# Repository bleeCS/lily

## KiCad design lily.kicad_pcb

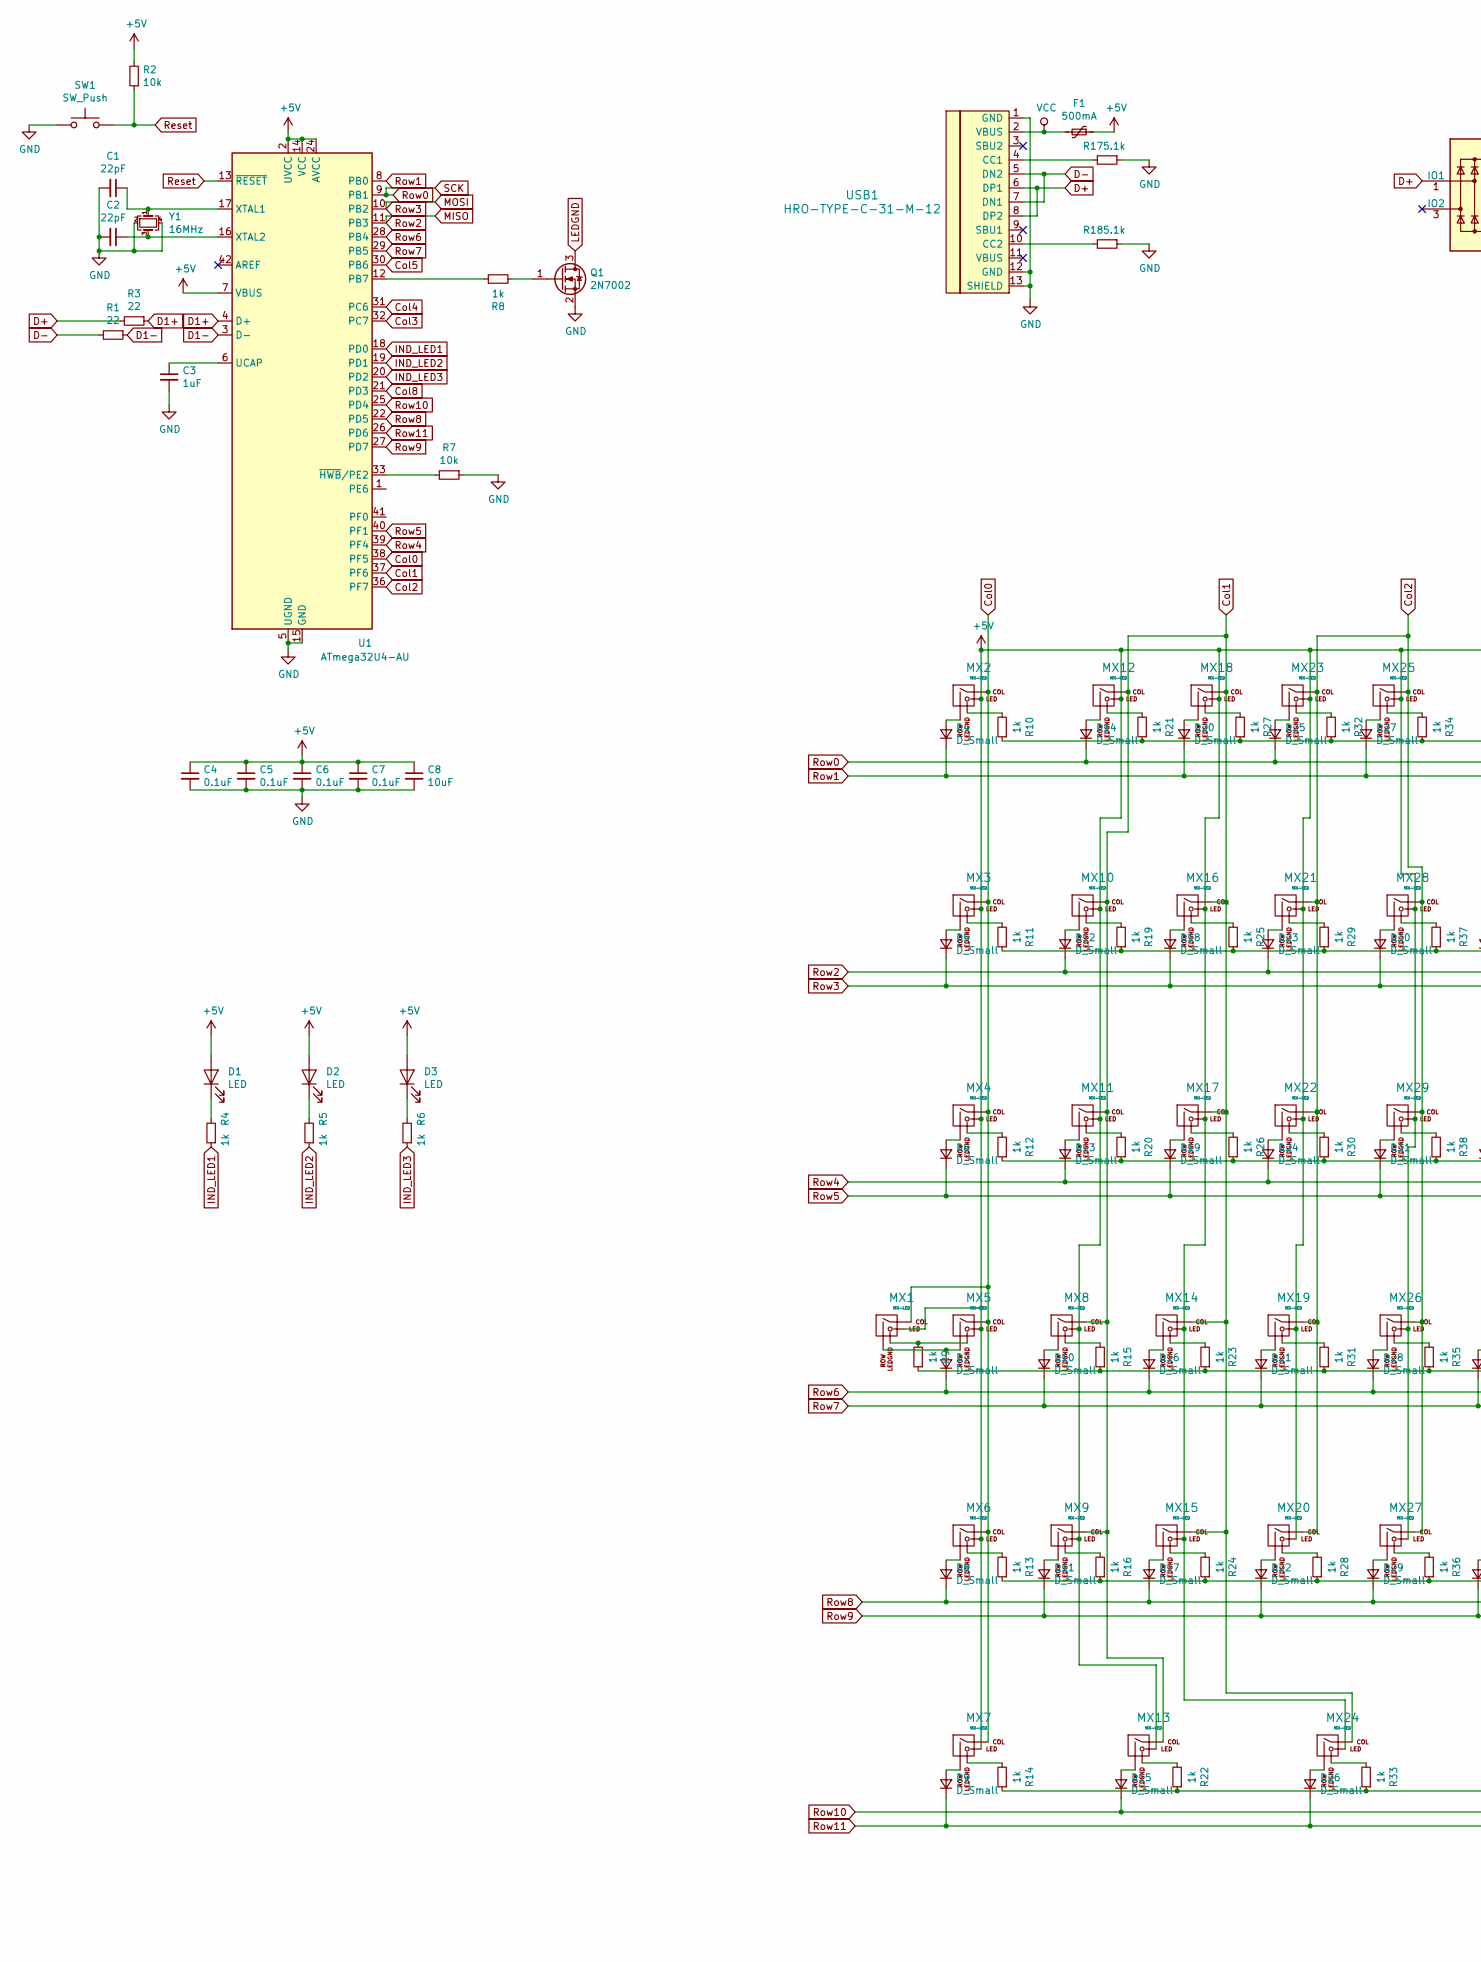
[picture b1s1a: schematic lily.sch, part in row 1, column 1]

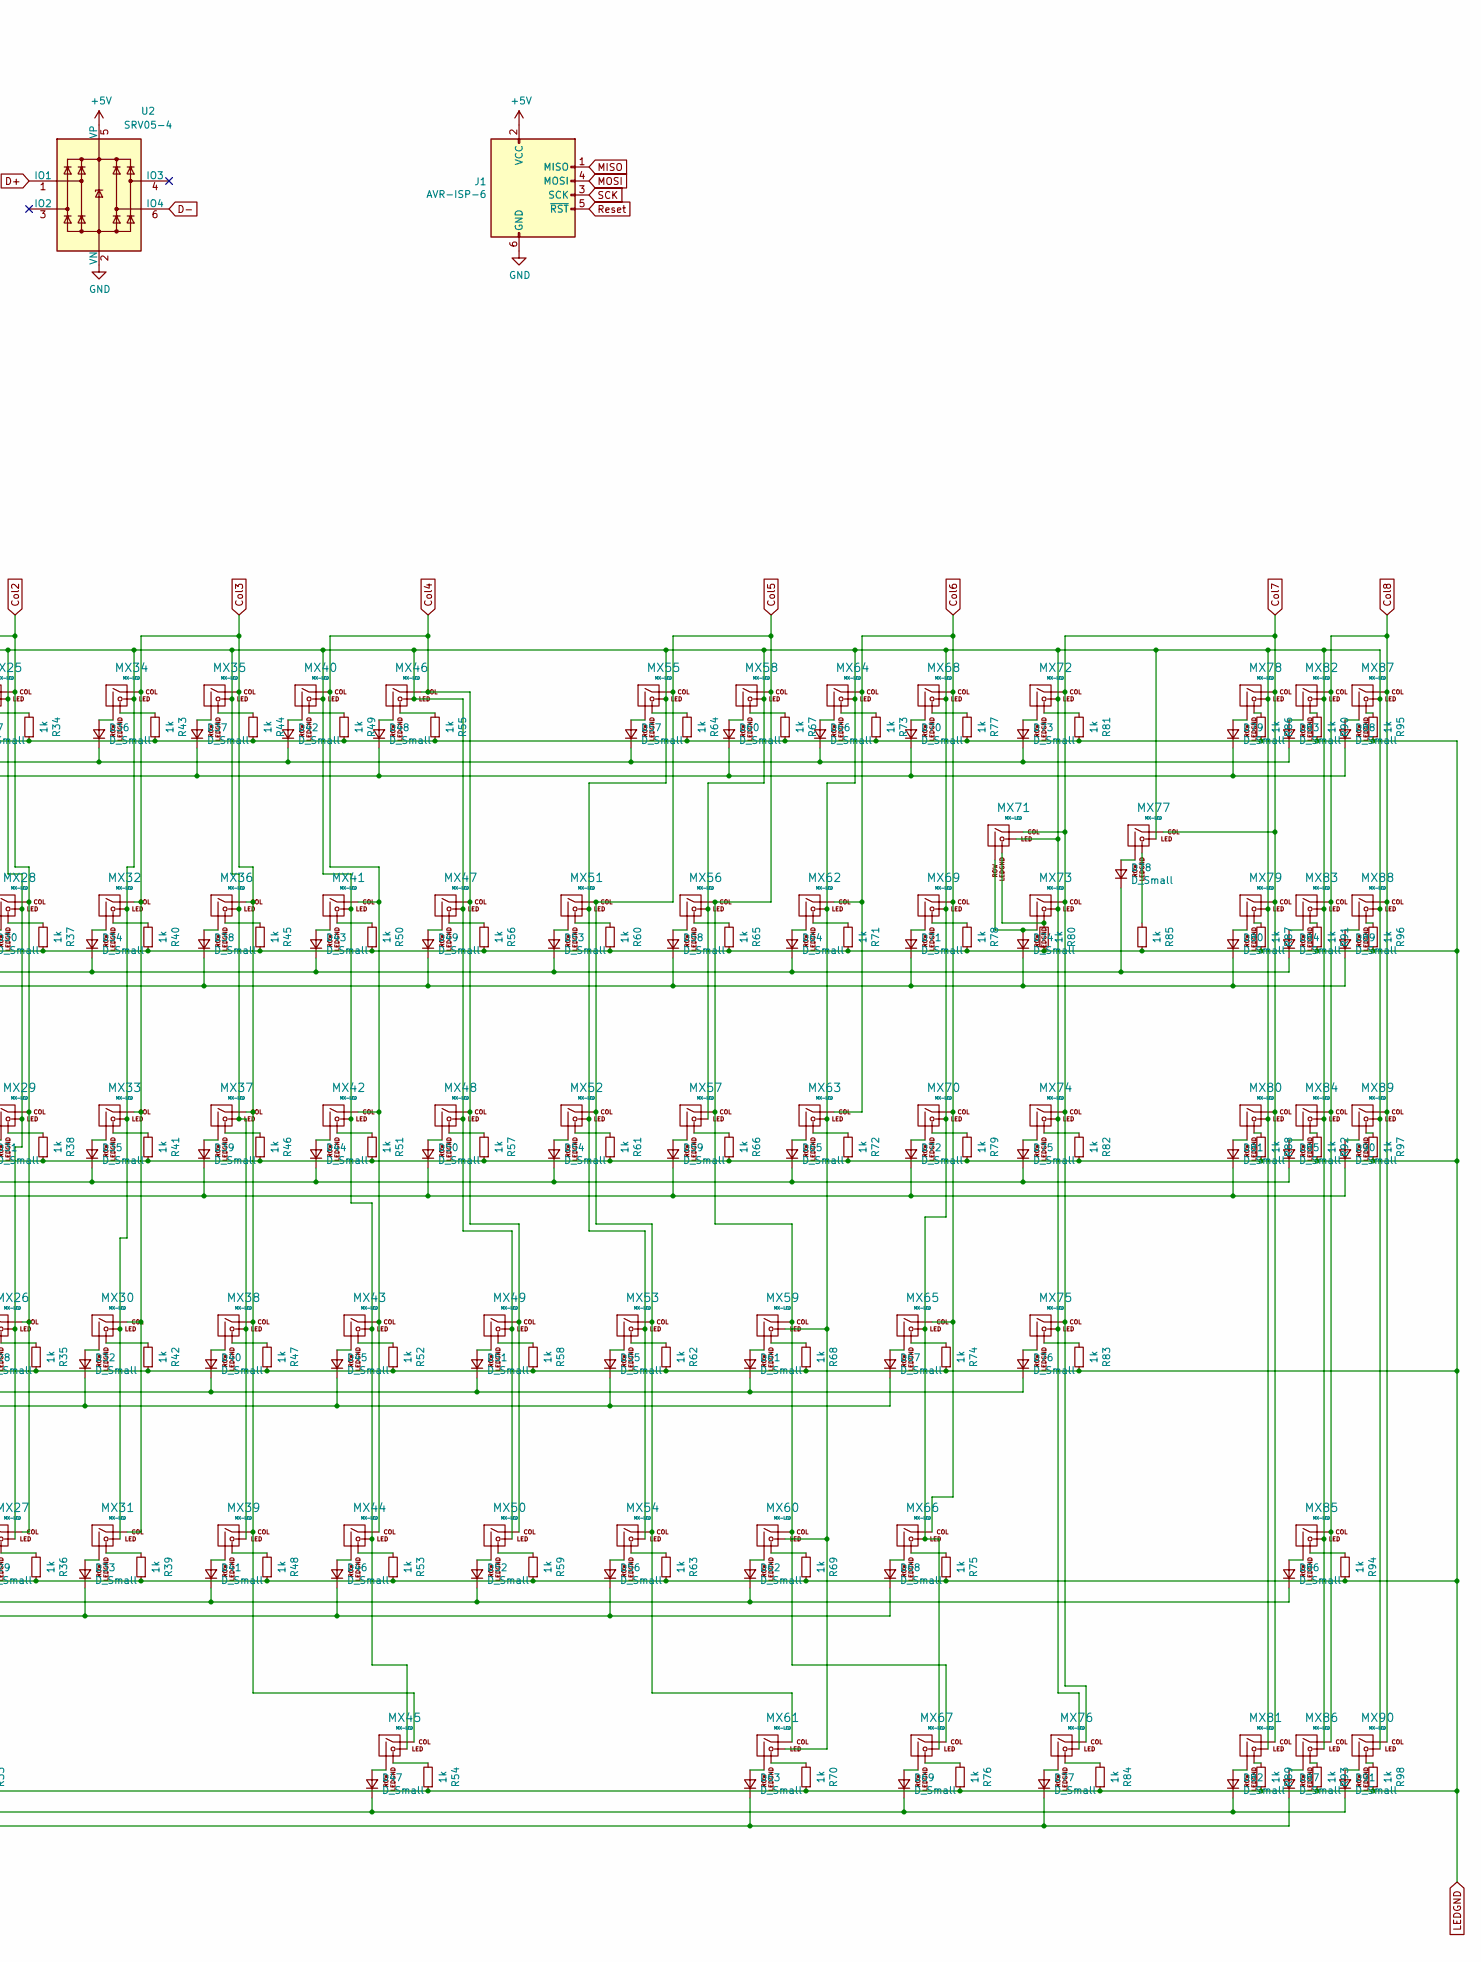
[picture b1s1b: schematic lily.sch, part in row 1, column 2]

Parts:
C1, C2: 22pF; C_0805_2012Metric
C3: 1uF; C_0805_2012Metric
C4, C5, C6, C7: 0.1uF; C_0805_2012Metric
C8: 10uF; C_0805_2012Metric
D1, D2, D3: LED; LED_D1.8mm_W3.3mm_H2.4mm
D4, D5, D6, D7, D8, D9, D10, D11, D12, D13, D14, D15, D16, D17, D18, D19, D20, D21, D22, D23, D24, D25, D26, D27, D28, D29, D30, D31, D32, D33, D34, D35, D36, D37, D38, D39, D40, D41, D42, D43, D44, D45, D46, D47, D48, D49, D50, D51, D52, D53, D54, D55, D56, D57, D58, D59, D60, D61, D62, D63, D64, D65, D66, D67, D68, D69, D70, D71, D72, D73, D74, D75, D76, D77, D78, D79, D80, D81, D82, D83, D84, D85, D86, D87, D88, D89, D90, D91: D_Small; D_SOD-123
F1: 500mA; Fuse_1206_3216Metric
J1: AVR-ISP-6; PinHeader_2x03_P1.00mm_Vertical
MX1: MX-LED; MXOnly-1.25U
MX2, MX3, MX8, MX9, MX10, MX11, MX12, MX13, MX14, MX15, MX16, MX17, MX18, MX19, MX20, MX21, MX22, MX23, MX25, MX26, MX27, MX28, MX29, MX30, MX31, MX32, MX33, MX34, MX35, MX36, MX37, MX38, MX39, MX40, MX41, MX42, MX43, MX44, MX46, MX47, MX48, MX49, MX50, MX51, MX52, MX53, MX54, MX55, MX56, MX57, MX58, MX59, MX60, MX62, MX63, MX64, MX65, MX67, MX68, MX69, MX70, MX71, MX72, MX77, MX78, MX79, MX80, MX81, MX82, MX83, MX84, MX85, MX86, MX87, MX88, MX89, MX90: MX-LED; MXOnly-1U
MX4, MX7, MX24, MX61, MX74, MX76: MX-LED; MXOnly-1.5U
MX5: MX-LED; MXOnly-1.75U
MX6: MX-LED; MXOnly-2.25U
MX45: MX-LED; MXOnly-7U-ReversedStabilizers
MX66: MX-LED; MXOnly-2.75U
MX73: MX-LED; MXOnly-2U
MX75: MX-LED; MXOnly-2.25U-ReversedStabilizers
Q1: 2N7002; SOT-23
R1, R3: 22; R_0805_2012Metric
R2, R7: 10k; R_0805_2012Metric
R4, R5, R6, R8, R9, R10, R11, R12, R13, R14, R15, R16, R19, R20, R21, R22, R23, R24, R25, R26, R27, R28, R29, R30, R31, R32, R33, R34, R35, R36, R37, R38, R39, R40, R41, R42, R43, R44, R45, R46, R47, R48, R49, R50, R51, R52, R53, R54, R55, R56, R57, R58, R59, R60, R61, R62, R63, R64, R65, R66, R67, R68, R69, R70, R71, R72, R73, R74, R75, R76, R77, R78, R79, R80, R81, R82, R83, R84, R85, R86, R87, R88, R89, R90, R91, R92, R93, R94, R95, R96, R97, R98: 1k; R_0805_2012Metric
R17, R18: 5.1k; R_0805_2012Metric
SW1: SW_Push; SKQG-1155865
U1: ATmega32U4-AU; TQFP-44_10x10mm_P0.8mm
U2: SRV05-4; SOT-23-6
USB1: HRO-TYPE-C-31-M-12
Y1: 16MHz; Crystal_SMD_3225-4Pin_3.2x2.5mm

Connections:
+5V: C4.1, C5.1, C6.1, C7.1, C8.1, D1.2 (A), D2.2 (A), D3.2 (A), F1.1, J1.2 (VCC), MX1.3 (LED), MX2.3 (LED), MX3.3 (LED), MX4.3 (LED), MX5.3 (LED), MX6.3 (LED), MX7.3 (LED), MX8.3 (LED), MX9.3 (LED), MX10.3 (LED), MX11.3 (LED), MX12.3 (LED), MX13.3 (LED), MX14.3 (LED), MX15.3 (LED), MX16.3 (LED), MX17.3 (LED), MX18.3 (LED), MX19.3 (LED), MX20.3 (LED), MX21.3 (LED), MX22.3 (LED), MX23.3 (LED), MX24.3 (LED), MX25.3 (LED), MX26.3 (LED), MX27.3 (LED), MX28.3 (LED), MX29.3 (LED), MX30.3 (LED), MX31.3 (LED), MX32.3 (LED), MX33.3 (LED), MX34.3 (LED), MX35.3 (LED), MX36.3 (LED), MX37.3 (LED), MX38.3 (LED), MX39.3 (LED), MX40.3 (LED), MX41.3 (LED), MX42.3 (LED), MX43.3 (LED), MX44.3 (LED), MX45.3 (LED), MX46.3 (LED), MX47.3 (LED), MX48.3 (LED), MX49.3 (LED), MX50.3 (LED), MX51.3 (LED), MX52.3 (LED), MX53.3 (LED), MX54.3 (LED), MX55.3 (LED), MX56.3 (LED), MX57.3 (LED), MX58.3 (LED), MX59.3 (LED), MX60.3 (LED), MX61.3 (LED), MX62.3 (LED), MX63.3 (LED), MX64.3 (LED), MX65.3 (LED), MX66.3 (LED), MX67.3 (LED), MX68.3 (LED), MX69.3 (LED), MX70.3 (LED), MX71.3 (LED), MX72.3 (LED), MX73.3 (LED), MX74.3 (LED), MX75.3 (LED), MX76.3 (LED), MX77.3 (LED), MX78.3 (LED), MX79.3 (LED), MX80.3 (LED), MX81.3 (LED), MX82.3 (LED), MX83.3 (LED), MX84.3 (LED), MX85.3 (LED), MX86.3 (LED), MX87.3 (LED), MX88.3 (LED), MX89.3 (LED), MX90.3 (LED), R2.2, U1.2 (UVCC), U1.7 (VBUS), U1.14 (VCC), U1.24 (AVCC), U1.34 (VCC), U1.44 (AVCC), U2.5 (VP)
Col0: MX1.1 (COL), MX2.1 (COL), MX3.1 (COL), MX4.1 (COL), MX5.1 (COL), MX6.1 (COL), MX7.1 (COL), U1.38 (PF5)
Col1: MX8.1 (COL), MX9.1 (COL), MX10.1 (COL), MX11.1 (COL), MX12.1 (COL), MX13.1 (COL), MX14.1 (COL), MX15.1 (COL), MX16.1 (COL), MX17.1 (COL), MX18.1 (COL), MX24.1 (COL), U1.37 (PF6)
Col2: MX19.1 (COL), MX20.1 (COL), MX21.1 (COL), MX22.1 (COL), MX23.1 (COL), MX25.1 (COL), MX26.1 (COL), MX27.1 (COL), MX28.1 (COL), MX29.1 (COL), U1.36 (PF7)
Col3: MX30.1 (COL), MX31.1 (COL), MX32.1 (COL), MX33.1 (COL), MX34.1 (COL), MX35.1 (COL), MX36.1 (COL), MX37.1 (COL), MX38.1 (COL), MX39.1 (COL), MX45.1 (COL), U1.32 (PC7)
Col4: MX40.1 (COL), MX41.1 (COL), MX42.1 (COL), MX43.1 (COL), MX44.1 (COL), MX46.1 (COL), MX47.1 (COL), MX48.1 (COL), MX49.1 (COL), MX50.1 (COL), U1.31 (PC6)
Col5: MX51.1 (COL), MX52.1 (COL), MX53.1 (COL), MX54.1 (COL), MX55.1 (COL), MX56.1 (COL), MX57.1 (COL), MX58.1 (COL), MX59.1 (COL), MX60.1 (COL), MX61.1 (COL), MX67.1 (COL), U1.30 (PB6)
Col6: MX62.1 (COL), MX63.1 (COL), MX64.1 (COL), MX65.1 (COL), MX66.1 (COL), MX68.1 (COL), MX69.1 (COL), MX70.1 (COL)
Col7: MX71.1 (COL), MX72.1 (COL), MX73.1 (COL), MX74.1 (COL), MX75.1 (COL), MX76.1 (COL), MX77.1 (COL), MX78.1 (COL), MX79.1 (COL), MX80.1 (COL), MX81.1 (COL)
Col8: MX82.1 (COL), MX83.1 (COL), MX84.1 (COL), MX85.1 (COL), MX86.1 (COL), MX87.1 (COL), MX88.1 (COL), MX89.1 (COL), MX90.1 (COL), U1.21 (PD3)
D1+: R3.1, U1.4 (D+)
D1-: R1.1, U1.3 (D-)
D+: R3.2, U2.1 (IO1), USB1.6 (DP1), USB1.8 (DP2)
D-: R1.2, U2.6 (IO4), USB1.5 (DN2), USB1.7 (DN1)
GND: C1.2, C2.2, C3.2, C4.2, C5.2, C6.2, C7.2, C8.2, J1.6 (GND), Q1.2 (S), R7.1, R17.1, R18.1, SW1.1, U1.5 (UGND), U1.15 (GND), U1.23 (GND), U1.35 (GND), U1.43 (GND), U2.2 (VN), USB1.1 (GND), USB1.12 (GND), USB1.13 (SHIELD), Y1.2, Y1.4
IND_LED1: R4.1, U1.18 (PD0)
IND_LED2: R5.1, U1.19 (PD1)
IND_LED3: R6.1, U1.20 (PD2)
LEDGND: Q1.3 (D), R9.1, R10.1, R11.1, R12.1, R13.1, R14.1, R15.1, R16.1, R19.1, R20.1, R21.1, R22.1, R23.1, R24.1, R25.1, R26.1, R27.1, R28.1, R29.1, R30.1, R31.1, R32.1, R33.1, R34.1, R35.1, R36.1, R37.1, R38.1, R39.1, R40.1, R41.1, R42.1, R43.1, R44.1, R45.1, R46.1, R47.1, R48.1, R49.1, R50.1, R51.1, R52.1, R53.1, R54.1, R55.1, R56.1, R57.1, R58.1, R59.1, R60.1, R61.1, R62.1, R63.1, R64.1, R65.1, R66.1, R67.1, R68.1, R69.1, R70.1, R71.1, R72.1, R73.1, R74.1, R75.1, R76.1, R77.1, R78.1, R79.1, R80.1, R81.1, R82.1, R83.1, R84.1, R85.1, R86.1, R87.1, R88.1, R89.1, R90.1, R91.1, R92.1, R93.1, R94.1, R95.1, R96.1, R97.1, R98.1
MISO: D12.1 (K), D23.1 (K), D34.1 (K), D43.1 (K), D53.1 (K), D64.1 (K), D78.1 (K), D84.1 (K), J1.1 (MISO), U1.11 (PB3)
MOSI: D5.1 (K), D18.1 (K), D30.1 (K), D38.1 (K), D49.1 (K), D58.1 (K), D71.1 (K), D74.1 (K), D80.1 (K), D89.1 (K), J1.4 (MOSI), U1.10 (PB2)
unnamed: C1.1, U1.17 (XTAL1), Y1.1
unnamed: C2.1, U1.16 (XTAL2), Y1.3
unnamed: C3.1, U1.6 (UCAP)
unnamed: D1.1 (K), R4.2
unnamed: D2.1 (K), R5.2
unnamed: D3.1 (K), R6.2
unnamed: D4.2 (A), MX2.2 (ROW)
unnamed: D5.2 (A), MX3.2 (ROW)
unnamed: D6.2 (A), MX4.2 (ROW)
unnamed: D7.2 (A), MX1.2 (ROW), MX5.2 (ROW)
unnamed: D8.2 (A), MX6.2 (ROW)
unnamed: D9.2 (A), MX7.2 (ROW)
unnamed: D10.2 (A), MX8.2 (ROW)
unnamed: D11.2 (A), MX9.2 (ROW)
unnamed: D12.2 (A), MX10.2 (ROW)
unnamed: D13.2 (A), MX11.2 (ROW)
unnamed: D14.2 (A), MX12.2 (ROW)
unnamed: D15.2 (A), MX13.2 (ROW)
unnamed: D16.2 (A), MX14.2 (ROW)
unnamed: D17.2 (A), MX15.2 (ROW)
unnamed: D18.2 (A), MX16.2 (ROW)
unnamed: D19.2 (A), MX17.2 (ROW)
unnamed: D20.2 (A), MX18.2 (ROW)
unnamed: D21.2 (A), MX19.2 (ROW)
unnamed: D22.2 (A), MX20.2 (ROW)
unnamed: D23.2 (A), MX21.2 (ROW)
unnamed: D24.2 (A), MX22.2 (ROW)
unnamed: D25.2 (A), MX23.2 (ROW)
unnamed: D26.2 (A), MX24.2 (ROW)
unnamed: D27.2 (A), MX25.2 (ROW)
unnamed: D28.2 (A), MX26.2 (ROW)
unnamed: D29.2 (A), MX27.2 (ROW)
unnamed: D30.2 (A), MX28.2 (ROW)
unnamed: D31.2 (A), MX29.2 (ROW)
unnamed: D32.2 (A), MX30.2 (ROW)
unnamed: D33.2 (A), MX31.2 (ROW)
unnamed: D34.2 (A), MX32.2 (ROW)
unnamed: D35.2 (A), MX33.2 (ROW)
unnamed: D36.2 (A), MX34.2 (ROW)
unnamed: D37.2 (A), MX35.2 (ROW)
unnamed: D38.2 (A), MX36.2 (ROW)
unnamed: D39.2 (A), MX37.2 (ROW)
unnamed: D40.2 (A), MX38.2 (ROW)
unnamed: D41.2 (A), MX39.2 (ROW)
unnamed: D42.2 (A), MX40.2 (ROW)
unnamed: D43.2 (A), MX41.2 (ROW)
unnamed: D44.2 (A), MX42.2 (ROW)
unnamed: D45.2 (A), MX43.2 (ROW)
unnamed: D46.2 (A), MX44.2 (ROW)
unnamed: D47.2 (A), MX45.2 (ROW)
unnamed: D48.2 (A), MX46.2 (ROW)
unnamed: D49.2 (A), MX47.2 (ROW)
unnamed: D50.2 (A), MX48.2 (ROW)
unnamed: D51.2 (A), MX49.2 (ROW)
unnamed: D52.2 (A), MX50.2 (ROW)
unnamed: D53.2 (A), MX51.2 (ROW)
unnamed: D54.2 (A), MX52.2 (ROW)
unnamed: D55.2 (A), MX53.2 (ROW)
unnamed: D56.2 (A), MX54.2 (ROW)
unnamed: D57.2 (A), MX55.2 (ROW)
unnamed: D58.2 (A), MX56.2 (ROW)
unnamed: D59.2 (A), MX57.2 (ROW)
unnamed: D60.2 (A), MX58.2 (ROW)
unnamed: D61.2 (A), MX59.2 (ROW)
unnamed: D62.2 (A), MX60.2 (ROW)
unnamed: D63.2 (A), MX61.2 (ROW)
unnamed: D64.2 (A), MX62.2 (ROW)
unnamed: D65.2 (A), MX63.2 (ROW)
unnamed: D66.2 (A), MX64.2 (ROW)
unnamed: D67.2 (A), MX65.2 (ROW)
unnamed: D68.2 (A), MX66.2 (ROW)
unnamed: D69.2 (A), MX67.2 (ROW)
unnamed: D70.2 (A), MX68.2 (ROW)
unnamed: D71.2 (A), MX69.2 (ROW)
unnamed: D72.2 (A), MX70.2 (ROW)
unnamed: D73.2 (A), MX72.2 (ROW)
unnamed: D74.2 (A), MX71.2 (ROW), MX73.2 (ROW)
unnamed: D75.2 (A), MX74.2 (ROW)
unnamed: D76.2 (A), MX75.2 (ROW)
unnamed: D77.2 (A), MX76.2 (ROW)
unnamed: D78.2 (A), MX77.2 (ROW)
unnamed: D79.2 (A), MX78.2 (ROW)
unnamed: D80.2 (A), MX79.2 (ROW)
unnamed: D81.2 (A), MX80.2 (ROW)
unnamed: D82.2 (A), MX81.2 (ROW)
unnamed: D83.2 (A), MX82.2 (ROW)
unnamed: D84.2 (A), MX83.2 (ROW)
unnamed: D85.2 (A), MX84.2 (ROW)
unnamed: D86.2 (A), MX85.2 (ROW)
unnamed: D87.2 (A), MX86.2 (ROW)
unnamed: D88.2 (A), MX87.2 (ROW)
unnamed: D89.2 (A), MX88.2 (ROW)
unnamed: D90.2 (A), MX89.2 (ROW)
unnamed: D91.2 (A), MX90.2 (ROW)
unnamed: MX1.4 (LEDGND), MX5.4 (LEDGND), R9.2
unnamed: MX2.4 (LEDGND), R10.2
unnamed: MX3.4 (LEDGND), R11.2
unnamed: MX4.4 (LEDGND), R12.2
unnamed: MX6.4 (LEDGND), R13.2
unnamed: MX7.4 (LEDGND), R14.2
unnamed: MX8.4 (LEDGND), R15.2
unnamed: MX9.4 (LEDGND), R16.2
unnamed: MX10.4 (LEDGND), R19.2
unnamed: MX11.4 (LEDGND), R20.2
unnamed: MX12.4 (LEDGND), R21.2
unnamed: MX13.4 (LEDGND), R22.2
unnamed: MX14.4 (LEDGND), R23.2
unnamed: MX15.4 (LEDGND), R24.2
unnamed: MX16.4 (LEDGND), R25.2
unnamed: MX17.4 (LEDGND), R26.2
unnamed: MX18.4 (LEDGND), R27.2
unnamed: MX19.4 (LEDGND), R31.2
unnamed: MX20.4 (LEDGND), R28.2
unnamed: MX21.4 (LEDGND), R29.2
unnamed: MX22.4 (LEDGND), R30.2
unnamed: MX23.4 (LEDGND), R32.2
unnamed: MX24.4 (LEDGND), R33.2
unnamed: MX25.4 (LEDGND), R34.2
unnamed: MX26.4 (LEDGND), R35.2
unnamed: MX27.4 (LEDGND), R36.2
unnamed: MX28.4 (LEDGND), R37.2
unnamed: MX29.4 (LEDGND), R38.2
unnamed: MX30.4 (LEDGND), R42.2
unnamed: MX31.4 (LEDGND), R39.2
unnamed: MX32.4 (LEDGND), R40.2
unnamed: MX33.4 (LEDGND), R41.2
unnamed: MX34.4 (LEDGND), R43.2
unnamed: MX35.4 (LEDGND), R44.2
unnamed: MX36.4 (LEDGND), R45.2
unnamed: MX37.4 (LEDGND), R46.2
unnamed: MX38.4 (LEDGND), R47.2
unnamed: MX39.4 (LEDGND), R48.2
unnamed: MX40.4 (LEDGND), R49.2
unnamed: MX41.4 (LEDGND), R50.2
unnamed: MX42.4 (LEDGND), R51.2
unnamed: MX43.4 (LEDGND), R52.2
unnamed: MX44.4 (LEDGND), R53.2
unnamed: MX45.4 (LEDGND), R54.2
unnamed: MX46.4 (LEDGND), R55.2
unnamed: MX47.4 (LEDGND), R56.2
unnamed: MX48.4 (LEDGND), R57.2
unnamed: MX49.4 (LEDGND), R58.2
unnamed: MX50.4 (LEDGND), R59.2
unnamed: MX51.4 (LEDGND), R60.2
unnamed: MX52.4 (LEDGND), R61.2
unnamed: MX53.4 (LEDGND), R62.2
unnamed: MX54.4 (LEDGND), R63.2
unnamed: MX55.4 (LEDGND), R64.2
unnamed: MX56.4 (LEDGND), R65.2
unnamed: MX57.4 (LEDGND), R66.2
unnamed: MX58.4 (LEDGND), R67.2
unnamed: MX59.4 (LEDGND), R68.2
unnamed: MX60.4 (LEDGND), R69.2
unnamed: MX61.4 (LEDGND), R70.2
unnamed: MX62.4 (LEDGND), R71.2
unnamed: MX63.4 (LEDGND), R72.2
unnamed: MX64.4 (LEDGND), R73.2
unnamed: MX65.4 (LEDGND), R74.2
unnamed: MX66.4 (LEDGND), R75.2
unnamed: MX67.4 (LEDGND), R76.2
unnamed: MX68.4 (LEDGND), R77.2
unnamed: MX69.4 (LEDGND), R78.2
unnamed: MX70.4 (LEDGND), R79.2
unnamed: MX71.4 (LEDGND), MX73.4 (LEDGND), R80.2
unnamed: MX72.4 (LEDGND), R81.2
unnamed: MX74.4 (LEDGND), R82.2
unnamed: MX75.4 (LEDGND), R83.2
unnamed: MX76.4 (LEDGND), R84.2
unnamed: MX77.4 (LEDGND), R85.2
unnamed: MX78.4 (LEDGND), R86.2
unnamed: MX79.4 (LEDGND), R87.2
unnamed: MX80.4 (LEDGND), R88.2
unnamed: MX81.4 (LEDGND), R89.2
unnamed: MX82.4 (LEDGND), R90.2
unnamed: MX83.4 (LEDGND), R91.2
unnamed: MX84.4 (LEDGND), R92.2
unnamed: MX85.4 (LEDGND), R94.2
unnamed: MX86.4 (LEDGND), R93.2
unnamed: MX87.4 (LEDGND), R95.2
unnamed: MX88.4 (LEDGND), R96.2
unnamed: MX89.4 (LEDGND), R97.2
unnamed: MX90.4 (LEDGND), R98.2
unnamed: Q1.1 (G), R8.2
unnamed: R7.2, U1.33 (~HWB~/PE2)
unnamed: R8.1, U1.12 (PB7)
unnamed: R17.2, USB1.4 (CC1)
unnamed: R18.2, USB1.10 (CC2)
Reset: J1.5 (~RST), R2.1, SW1.2, U1.13 (~RESET)
Row0: D14.1 (K), D25.1 (K), D36.1 (K), D42.1 (K), D57.1 (K), D66.1 (K), D73.1 (K), D83.1 (K), J1.3 (SCK), U1.9 (PB1)
Row1: D4.1 (K), D20.1 (K), D27.1 (K), D37.1 (K), D48.1 (K), D60.1 (K), D70.1 (K), D79.1 (K), D88.1 (K), U1.8 (PB0)
Row4: D13.1 (K), D24.1 (K), D35.1 (K), D44.1 (K), D54.1 (K), D65.1 (K), D75.1 (K), D85.1 (K), U1.39 (PF4)
Row5: D6.1 (K), D19.1 (K), D31.1 (K), D39.1 (K), D50.1 (K), D59.1 (K), D72.1 (K), D81.1 (K), D90.1 (K), U1.40 (PF1)
Row6: D7.1 (K), D16.1 (K), D28.1 (K), D40.1 (K), D51.1 (K), D61.1 (K), D76.1 (K), U1.28 (PB4)
Row7: D10.1 (K), D21.1 (K), D32.1 (K), D45.1 (K), D55.1 (K), D67.1 (K), U1.29 (PB5)
Row8: D8.1 (K), D17.1 (K), D29.1 (K), D41.1 (K), D52.1 (K), D62.1 (K), D86.1 (K), U1.22 (PD5)
Row9: D11.1 (K), D22.1 (K), D33.1 (K), D46.1 (K), D56.1 (K), D68.1 (K), U1.27 (PD7)
Row10: D15.1 (K), D47.1 (K), D69.1 (K), D82.1 (K), D91.1 (K), U1.25 (PD4)
Row11: D9.1 (K), D26.1 (K), D63.1 (K), D77.1 (K), D87.1 (K), U1.26 (PD6)
VCC: F1.2, USB1.2 (VBUS)

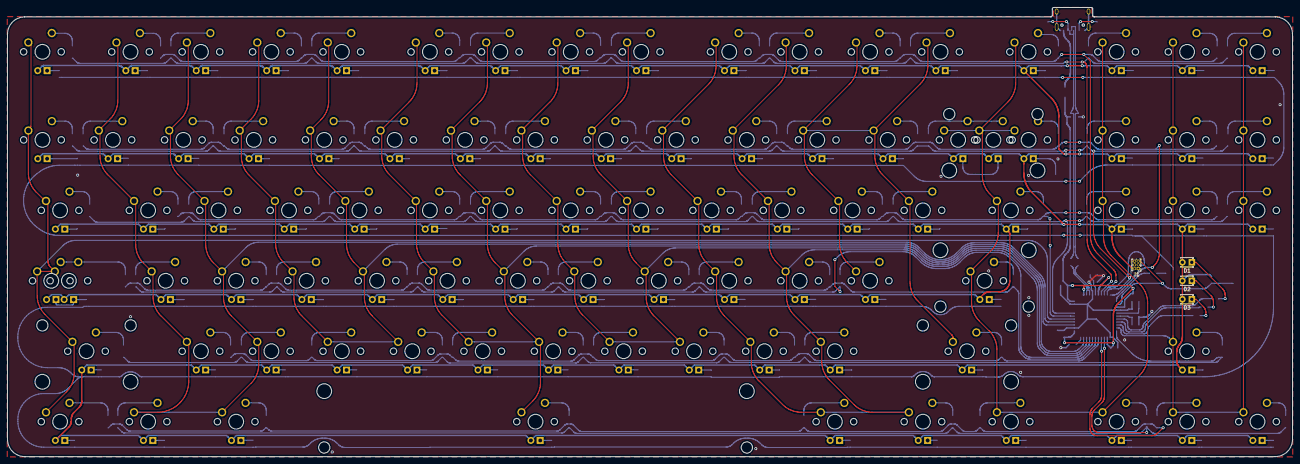
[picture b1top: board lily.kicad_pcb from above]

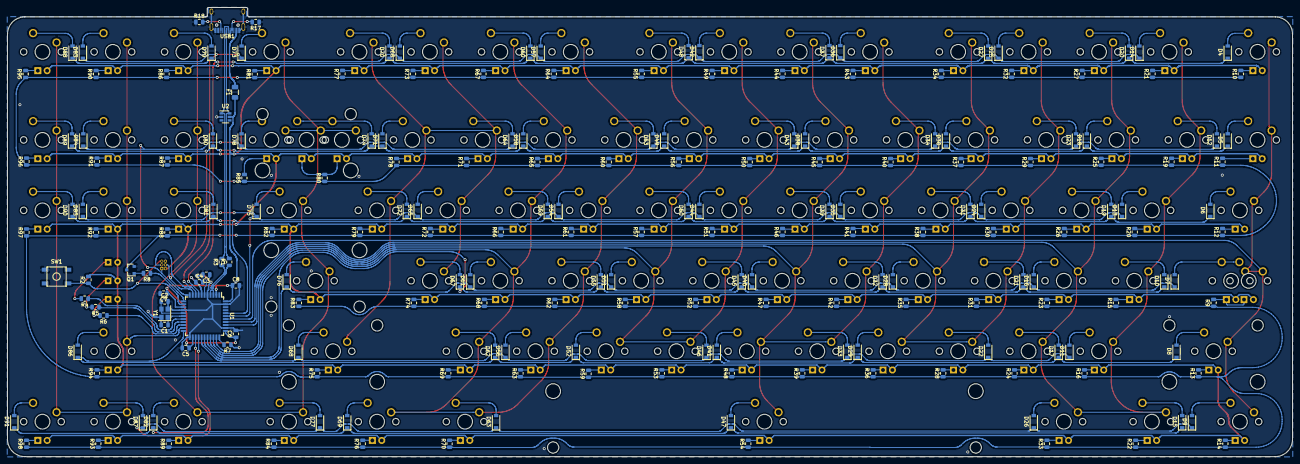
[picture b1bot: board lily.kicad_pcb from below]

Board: 2 copper layers, 347.5 x 121.5 mm, 295 parts (201 on the bottom side), 220 nets.

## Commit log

2020-05-29 lots of things
2020-05-29 add readme
2020-06-04 wrapping things up. ready for review.
